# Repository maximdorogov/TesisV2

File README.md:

# TesisV2
FPGA Modules used in my electronic engineering thesis

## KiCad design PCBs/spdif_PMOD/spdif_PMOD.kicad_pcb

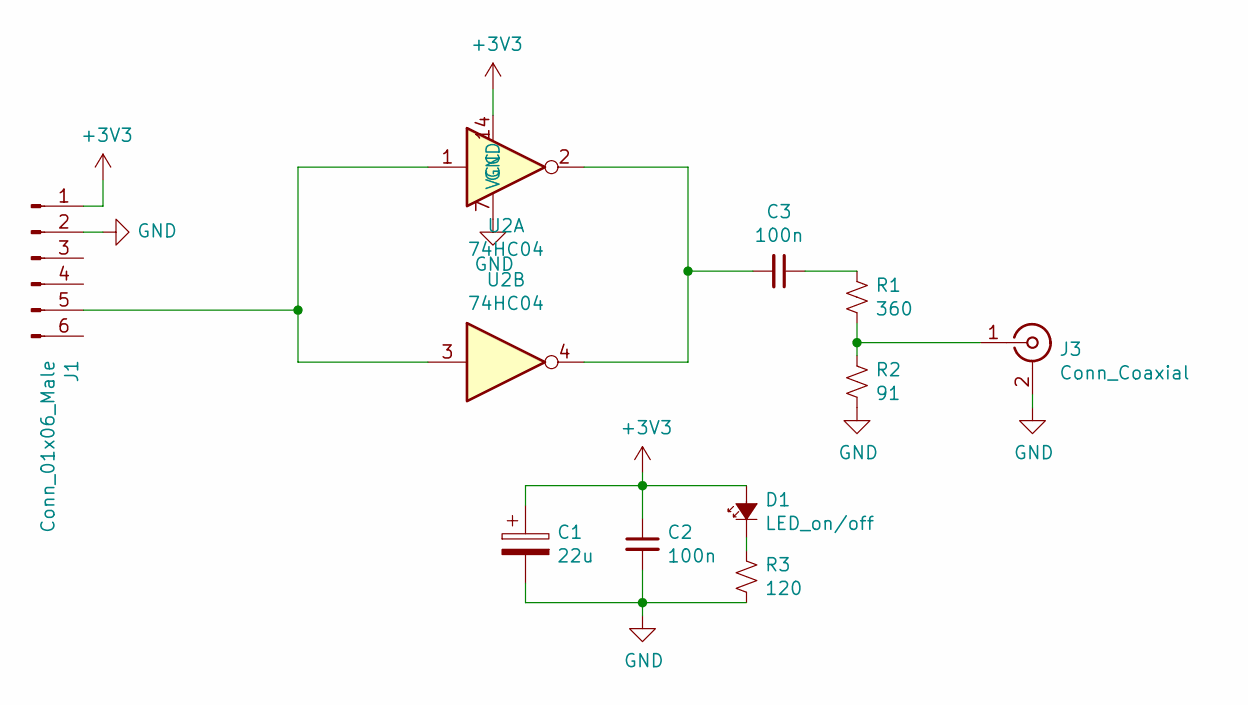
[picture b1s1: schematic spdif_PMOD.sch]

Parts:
C1: 22u; CP_Radial_D4.0mm_P2.00mm
C2, C3: 100n; C_Disc_D7.5mm_W4.4mm_P5.00mm
D1: LED_on/off; LED_D3.0mm
J1: Conn_01x06_Male; PinHeader_1x06_P2.54mm_Horizontal
J3: Conn_Coaxial; BarrelJack_CUI_PJ-063AH_Horizontal
R1: 360; R_Axial_DIN0207_L6.3mm_D2.5mm_P7.62mm_Horizontal
R2: 91; R_Axial_DIN0207_L6.3mm_D2.5mm_P7.62mm_Horizontal
R3: 120; R_Axial_DIN0207_L6.3mm_D2.5mm_P7.62mm_Horizontal
U2: 74HC04; DIP-14_W7.62mm_LongPads

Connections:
+3V3: C1.1, C2.1, D1.2 (A), J1.1, U2.14 (VCC)
GND: C1.2, C2.2, J1.2, J3.2 (Ext), R2.2, R3.2, U2.7 (GND)
unnamed: C3.1, R1.1
unnamed: C3.2, U2.2, U2.4
unnamed: D1.1 (K), R3.1
unnamed: J1.5, U2.1, U2.3
unnamed: J3.1 (In), R1.2, R2.1

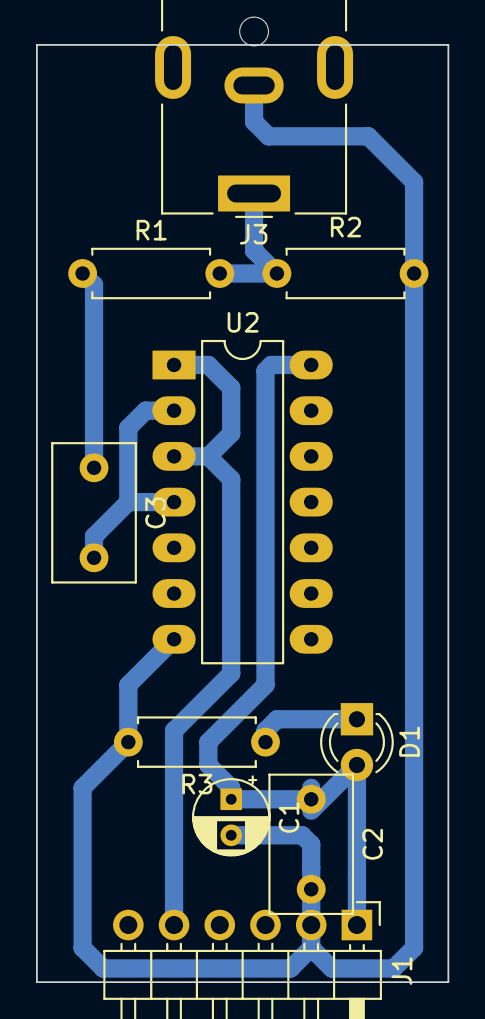
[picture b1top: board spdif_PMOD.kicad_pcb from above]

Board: 2 copper layers, 22.9 x 52.1 mm, 10 parts (0 on the bottom side), 7 nets.

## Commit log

2019-11-02 agrego proyecto de vivado con salida spdif
2019-11-02 meto todo en una sola carpeta
2019-11-03 Agrego sintesis y resultados del ILA
2019-11-03 agrego sintesis y resultados ILA
2019-11-04 spdif OSVA y spdifV2 terminados
2019-11-09 agrego PCB's del adc y salida spdif
2019-11-10 agrego PCB spdif_pmod terminado
2019-11-21 agrego modulo controlador del ADC
